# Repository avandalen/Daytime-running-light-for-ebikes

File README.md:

See the whole article here: https://www.avdweb.nl/solar-bike/electronics/daytime-running-light

Why daytime running lights?

Cars are an increasing danger to cyclists. This is because the motorist is distracted by operating the abundant of electronics in the car, such as navigation, smartphone, etc. A car sometimes looks like an airplane cockpit, with the difference that in an airplane there is a co-pilot to operate everything.

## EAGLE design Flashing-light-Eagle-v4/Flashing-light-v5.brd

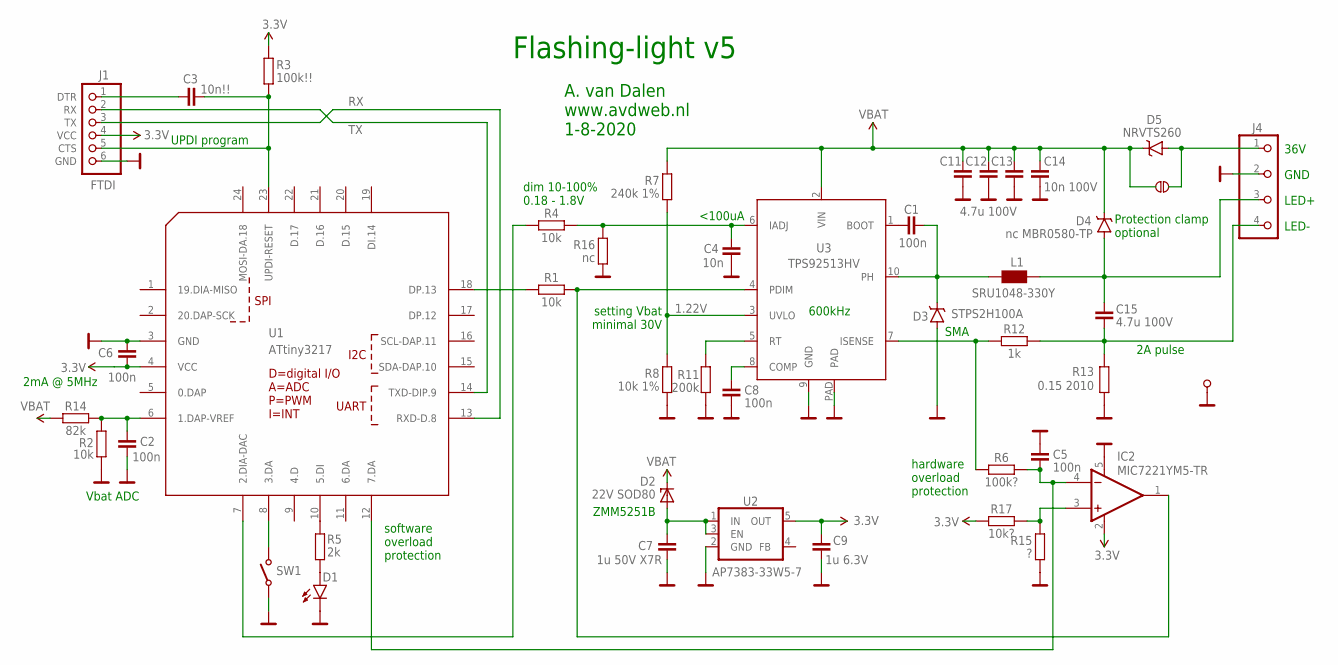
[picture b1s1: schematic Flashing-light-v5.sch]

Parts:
C1: 100n; 0805-CAP
C2, C5, C6, C8: 100n; 0603-SMALL
C3: 10n!!; 0603-SMALL
C4: 10n; 0603-SMALL
C7: 1u 50V X7R; 0805-CAP
C9: 1u 6.3V; 0603-SMALL
C11, C12, C13, C15: 4.7u 100V; 1210
C14: 10n 100V; 0603-SMALL
D1: green; LED-0603
D2: 22V SOD80; SOD80C
D3: STPS2H100A; SMA
D4: nc MBR0580-TP; SOD-123
D5: NRVTS260; SOD-123
IC2: MIC7221YM5-TR; SOT23-5L
J1: FTDI; ZIGZAG-FTDI
J3: TP; PIN-1.2MM
J4: CON-4PHEADER; 1X04
JP1: nc; JUMPER_NO
L1: SRU1048-330Y; IND-10X10
R1, R2, R4: 10k; 0603-SMALL
R3: 100k!!; 0603-SMALL
R5: 2k; 0603-SMALL
R6: 100k?; 0603-SMALL
R7: 240k 1%; 0603-SMALL
R8: 10k 1%; 0603-SMALL
R11: 200k; 0603-SMALL
R12: 1k; 0603-SMALL
R13: 0.15 2010; R2010
R14: 82k; 0603-SMALL
R15: ?; 0603-SMALL
R16: nc; 0603-SMALL
R17: 10k?; 0603-SMALL
SW1: TACTILE; TACTILE-PTH
U1: ATtiny3217; QFN-24
U2: AP7383-33W5-7; SOT23-5
U3: TPS92513HV; HVSS0P-10

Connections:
0.5V: R11.2, U3.5 (RT)
1.22V: R7.1, R8.2, U3.3 (UVLO)
3.3V: C6.2, C9.1, IC2.2 (V+), J1.4 (VCC), R3.2, R17.1, U1.4 (VCC), U2.5 (OUT)
ADC: C2.1, R2.2, R14.1, U1.6 (1.DAP-VREF)
GND: C2.2, C4.2, C5.1, C6.1, C7.2, C8.2, C9.2, C11.2, C12.2, C13.2, C14.2, D1.C, D3.A, IC2.5 (V-), J1.6 (GND), J3.1, J4.2, R2.1, R8.1, R11.1, R13.1, R15.1, R16.1, SW1.3, SW1.4, U1.3 (GND), U2.2 (GND), U3.9 (GND), U3.PAD
unnamed: R6.1, R12.1, U3.7 (ISENSE)
unnamed: C15.2, J4.4, R12.2, R13.2
unnamed: D5.A, J4.1, JP1.2, JP1.2B (2)
unnamed: C1.1, U3.1 (BOOT)
unnamed: R4.1, U1.7 (2.DIA-DAC)
unnamed: C15.1, D4.A, J4.3, L1.2
unnamed: C8.1, U3.8 (COMP)
unnamed: C7.1, D2.A, U2.1 (IN), U2.3 (EN)
unnamed: SW1.1 (O), SW1.2 (O), U1.8 (3.DA)
unnamed: R5.2, U1.10 (5.DI)
unnamed: C5.2, IC2.4 (-IN), R6.2, U1.12 (7.DA)
unnamed: D1.A, R5.1
unnamed: C4.1, R4.2, R16.2, U3.6 (IADJ)
unnamed: IC2.1 (OUT), R1.2, U3.4 (PDIM)
unnamed: IC2.3 (+IN), R15.2, R17.2
unnamed: R1.1, U1.18 (DP.13)
unnamed: C3.1, J1.1 (DTR)
PH: C1.2, D3.C, L1.1, U3.10 (PH)
RESET: C3.2, J1.5 (CTS), R3.1, U1.23 (UPDI-RESET)
RX: J1.3 (TX), U1.13 (RXD-D.8)
TX: J1.2 (RX), U1.14 (TXD-DIP.9)
VBAT: C11.1, C12.1, C13.1, C14.1, D2.C, D4.C, D5.C, JP1.1, JP1.1A (1), R7.2, R14.2, U3.2 (VIN)

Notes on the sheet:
A. van Dalen www.avdweb.nl 1-8-2020
Flashing-light v5
UPDI program
ZMM5251B
LED-
LED+
36V
GND
SMA
Protection clamp optional
setting Vbat minimal 30V
2A pulse
600kHz
Vbat ADC
dim 10-100% 0.18 - 1.8V
<100uA
hardware overload protection
2mA @ 5MHz
software overload protection

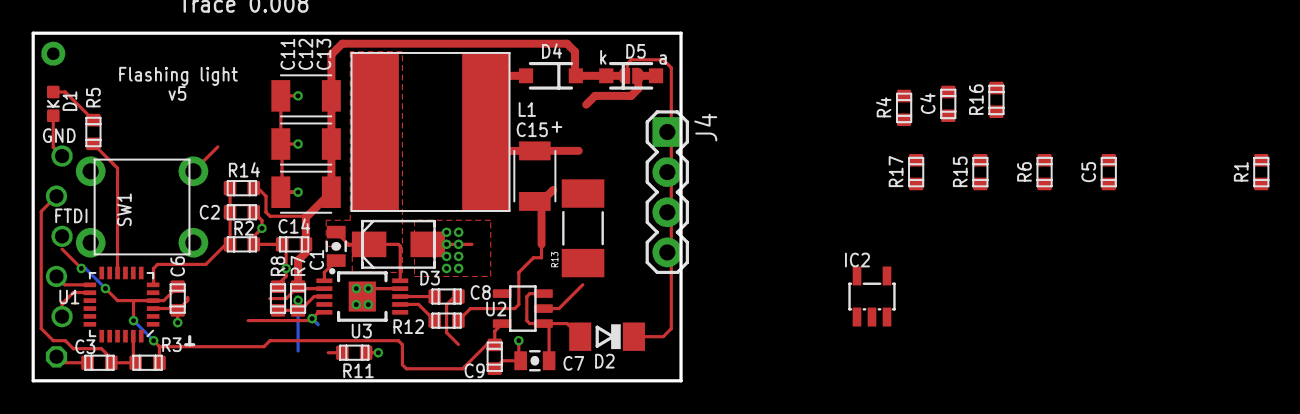
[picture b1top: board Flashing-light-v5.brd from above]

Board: 2 copper layers, 41.0 x 22.0 mm, 44 parts (0 on the bottom side), 27 nets.

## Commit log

2020-10-03 Create cc
2021-05-24 Create LICENSE
